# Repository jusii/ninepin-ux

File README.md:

# Ninepin UX

A USB and Bluetooth HID bridge for retro computers. USB and Bluetooth keyboards, mice and game
controllers on a Commodore Amiga or a C64, with the real Amiga keyboard passed through alongside
them. Over Wi-Fi, a PiKVM-compatible API lets scripts and LLM agents type and move the mouse.
Over USB-C the board is a USB adapter for a PC, a Mac or a C64 Ultimate.

Originally based on [borb/amigahid-pico](https://github.com/borb/amigahid-pico).

## boards

| board | what | state |
|---|---|---|
| **rev7.1** (`hardware/rev7.1/`) | rev7 + a reset supervisor on RUN (cold-plug fix) | current design, ordered |
| rev7 (tag `hw/ux-rev7`) | RP2350A + RM2 radio chip-down, 4 layers, 100 x 62 mm | built; needs the RUN bodge ([errata](./doc/errata.md)) |

rev7 and rev7.1 run the same firmware and fit the same case. Older boards: [history](./doc/history.md).

## features

* **Keyboard out** to the Amiga: mini-DIN6 (A4000D); DIN5 machines (A2000, A3000, A4000T) through
  a DIN5-to-mini-DIN6 cable; A500 header.
* **Real Amiga keyboard in** (mini-DIN6 or A500 header), merged with USB and Bluetooth input.
  Ctrl-Amiga-Amiga resets the Amiga for as long as it is held.
* **USB host** (USB-A, hubs): keyboards, mice, game controllers.
* **Bluetooth** (RM2 / CYW43439): Classic and LE keyboards, mice and controllers.
* **Game controllers:** PS5 DualSense (USB, Bluetooth), PS4 DualShock 4 (Bluetooth), PS3
  DualShock 3 (USB), generic HID pads. Two players, swap, merge, deadzone, autofire, DualSense
  touchpad as mouse.
* **Pad combos and profiles:** a pad button stands for directions and fire held together, a
  keyboard key, or both; 32 named profiles, each for the Amiga, the C64 or both, switched from
  the page, the menu or the pad.
* **Three modes:** `amiga` (keyboards to the Amiga, mouse and pads to the DE9 ports), `c64`
  (keyboard and mouse to USB-C, pads to the DE9 ports), `usb` (everything, the Amiga keyboard
  included, to USB-C for a PC or Mac).
* **DE9 ports, Amiga:** mouse (TankMouse / Cocolino wheel), joystick with 3 fire buttons, CD32 pad.
* **DE9 ports, C64:** joystick with 2nd / 3rd fire on the POT lines, 1351 mouse.
* **USB-C device:** keyboard, mouse, two gamepads, serial console.
* **Keyboard settings:** Help / Del / ISO key mapping, Y-Z and AZERTY presets, 8 remaps each way.
* **Menu** on the OLED, in two levels, from a keyboard, the BOOT button, a rotary encoder, a
  PlayStation pad or the console.
* **Wi-Fi:** access point or joins a network; settings page (no JavaScript) with every menu
  setting, a log-in with the page password, the board's uptime and why it last restarted.
* **Network control:** a subset of the PiKVM `kvmd` HTTP API (keys, text in six keymaps, mouse).
* **Firmware updates:** A/B slots with rollback; from the latest signed release on GitHub when
  asked, or a file uploaded on the settings page; with or without a press of BOOT on the board.

## docs

* [user guide](./doc/user-guide.md): connecting, first install, modes, menu, pads, Bluetooth,
  Wi-Fi, network control, updates.
* [board](./doc/board.md): connectors, power, encoder, OLED.
* [build](./doc/build.md): firmware build, ordering and assembling a board, the case.
* [errata](./doc/errata.md): read before building.
* [history](./doc/history.md): earlier boards and where their files are.

Firmware downloads: [Releases](https://github.com/jusii/ninepin-ux/releases).

## repository

| path | what |
|---|---|
| `firmware/` | firmware source, CMake build, pico-sdk and library submodules |
| `hardware/rev7.1/` | KiCad project and generator scripts, `fab/` (JLCPCB package), `bom/` (hand-fit parts, ibom) |
| `hardware/case/` | 3D-printable case (STL, STEP, FreeCAD) and its generator |
| `tools/` | board checkers, bench scripts |
| `doc/` | the guides above |

## credits

* **nine (borb)**: the original [amigahid](https://github.com/borb/amigahid) and
  [amigahid-pico](https://github.com/borb/amigahid-pico): the idea, the Amiga keyboard and
  quadrature code, the rev 2-5 boards.
* **Stefan Reinauer**: Bluetooth HID host, mouse-motion rewrite, input bridge, SDK/TinyUSB/CYW43
  update ([#44](https://github.com/borb/amigahid-pico/pull/44),
  [#47](https://github.com/borb/amigahid-pico/pull/47),
  [#48](https://github.com/borb/amigahid-pico/pull/48),
  [#49](https://github.com/borb/amigahid-pico/pull/49)). The settings store, gamepad parser, PS3,
  DualShock 4, CD32 and menu input handling are ported from his
  [reinauer/amigahid-pico](https://github.com/reinauer/amigahid-pico).
* **fboldog**: SH1106 1.3" OLED support ([#46](https://github.com/borb/amigahid-pico/pull/46)).
* **BennehBoy**, **rfuest**: keyboard fixes upstream.
* µgui by Achim Döbler, see the [display readme](./firmware/src/display/README.md).

An LLM assistant was used throughout this project, for the board layout, the checker scripts,
the firmware and these docs. Every result was reviewed, built and tested by hand.

## license

* Firmware and tools: Eclipse Public License 2.0 ([LICENSE](./LICENSE)), inherited from upstream.
* Hardware (`hardware/`: boards and case): CERN-OHL-W-2.0 ([hardware/LICENSE](./hardware/LICENSE)).

Jusii: boards, case, keyboard passthrough, rev7 firmware.

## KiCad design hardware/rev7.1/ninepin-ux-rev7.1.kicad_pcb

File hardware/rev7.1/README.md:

# Ninepin UX rev7.1

rev7 plus **U11, a TLV803S reset supervisor on RUN**. Same firmware, outline, connectors, case
(`../case/`) and hand-fitted parts as rev7 (tag `hw/ux-rev7`). Ordering and assembly:
[doc/build.md](../../doc/build.md).

## changes from rev7

* **U11 TLV803SDBZR (LCSC C132016) + C40 100 nF**, south of the OLED. U11 holds RUN low until 3V3
  has been above 2.93 V for 200 ms, and again whenever 3V3 sags below that: no more cold-plug
  BOOTSEL. Open drain, wired-OR with SW2 on `run_sw`. New copper is `route.py` block 5 only.
* R70/R71 use C25190, the same 27R as R57/R58.
* L1 is the Abracon AOTA-B201610S3R3-101-T the land was drawn for.
* `fab/make_fab.py`: JLC rotation offsets from the rev7 order preview; SMT-only recipe.

If U11 misbehaves: remove it and fit 1 µF + 1 MΩ across SW2 pins 1-2 on the back.

## regenerate and check

From the repository root. KiCad 10 with its Python `pcbnew`; FreeCAD for the case.

```shell
cd hardware/rev7.1 && python3 make_sch.py && python3 make_board.py --force && python3 route.py && cd ../..
P=hardware/rev7.1/ninepin-ux-rev7.1
kicad-cli sch erc $P.kicad_sch --exit-code-violations
kicad-cli pcb drc $P.kicad_pcb --schematic-parity --severity-all --refill-zones --save-board --exit-code-violations
git checkout -- $P.kicad_pro $P.kicad_prl     # kicad-cli rewrites them
python3 tools/check_rev7_1_pcb.py && python3 tools/check_rev7_1_netlist.py && python3 tools/check_rev7_1_style.py
python3 hardware/rev7.1/fab/make_fab.py       # SMT-only and full-assembly BOM/CPL; gerbers only re-cut if the board changed
python3 tools/check_rev7_1_fab.py             # the fab package matches the board
python3 hardware/case/run_case.py             # case STLs and fit report
```

`bom/ibom.html` comes from the InteractiveHtmlBom plugin
(`generate_interactive_bom.py --no-browser --dest-dir bom --name-format ibom --highlight-pin1 all
--checkboxes Sourced,Placed --bom-view top-bottom --layer-view F --show-fields Value,Footprint
--blacklist 'H*' ninepin-ux-rev7.1.kicad_pcb`).

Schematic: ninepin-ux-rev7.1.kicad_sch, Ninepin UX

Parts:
C1: 22uF; C_0805_2012Metric; LCSC C45783
C2, C6, C10, C14: 10uF; C_0805_2012Metric; LCSC C15850
C3, C5, C7, C11, C12, C13, C23, C24, C26, C27, C28, C32, C36: 100nF; C_0603_1608Metric; LCSC C14663
C4: 150uF; CP_Elec_6.3x7.7; MPN EEEFKC151XAP; LCSC C413656
C8, C9, C31: 1uF; C_0603_1608Metric; LCSC C15849
C20: 4.7uF; C_0402_1005Metric; LCSC C23733
C21, C22, C25, C30, C39, C40: 100nF; C_0402_1005Metric; LCSC C1525
C29, C38: 4.7uF; C_0402_1005Metric_vreg; LCSC C23733
C33, C34: 15pF; C_0603_1608Metric; LCSC C1644
C35: 4.7uF; C_0805_2012Metric; LCSC C1779
C37: 4.7uF; C_0603_1608Metric; LCSC C19666
D1, D2, D3: SS34; D_SMA; LCSC C8678
D4, D5, D6: B5819W; D_SOD-123; LCSC C8598
D10, D11, D12, D20, D21, D22, D23, D24, D25, D26, D27, D28, D29, D30: PESD5V0S1BA; D_SOD-323; LCSC C19224
D13, D14, D15, D16, D17, D18, D19: PESD5V0S1BL; D_SOD-882; MPN PESD5V0S1BL,315; LCSC C84374
F1: 750mA; Fuse_1812_4532Metric; MPN MF-MSMF075-2; LCSC C84140
F2, F3: 500mA; Fuse_1812_4532Metric; MPN MF-MSMF050-2; LCSC C17313
FB1: 600R@100MHz; L_0603_1608Metric; MPN BLM18AG601SN1D; LCSC C19330
J1: A500 KBD OUT; PinHeader_1x08_P2.54mm_Vertical; LCSC C492407
J2: SWD; PinHeader_1x03_P2.54mm_Vertical; LCSC C2937625
J3: OLED; PinSocket_1x04_P2.54mm_Vertical; MPN PM254-1-04-Z-8.5; LCSC C2897367
J4: USB-A HOST; USB_A_Molex_67643_Horizontal; MPN Molex 676432910; LCSC C564920
J7: ENCODER; PinHeader_2x03_P2.54mm_Vertical; MPN BOOMELE 2.54-2*3P; LCSC C65114
J8: A500 KBD IN; PinHeader_1x08_P2.54mm_Vertical; LCSC C492407
J10: KBD OUT (to Amiga); MiniDIN6_PS2_Socket_CUI_MD-60S; MPN CUI MD-60S; LCSC C6089346
J12: KBD IN (from keyboard); MiniDIN6_PS2_Socket_CUI_MD-60S; MPN CUI MD-60S; LCSC C6089346
J13: USB-C; USB_C_Receptacle_GCT_USB4105-xx-A_16P_TopMnt_Horizontal; MPN GCT USB4105-GF-A-120; LCSC C5184243
JP1: KBIN PWRLED; SolderJumper-2_P1.3mm_Open_RoundedPad1.0x1.5mm
L1: 3.3uH; L_2016_AOTA; MPN AOTA-B201610S3R3-101-T; LCSC C42411119
LED1: WS2812B-2020; LED_WS2812B-2020_PLCC4_2.0x2.0mm; LCSC C52917434
P1: DE9 PORT 1; DSUB-9_Pins_Horizontal_P2.77x2.84mm_EdgePinOffset7.70mm_Hou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; MPN TE 5747840-4; LCSC C305939
P2: DE9 PORT 2; DSUB-9_Pins_Horizontal_P2.77x2.84mm_EdgePinOffset7.70mm_Hou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; MPN TE 5747840-4; LCSC C305939
Q1: 2N7002; SOT-23; LCSC C8545
Q2, Q3: BSS138; SOT-23; LCSC C82045
R41, R42, R68: 4.7k; R_0603_1608Metric; LCSC C23162
R43, R44: 5.1k; R_0603_1608Metric; LCSC C23186
R45, R55: 470; R_0603_1608Metric; LCSC C23179
R46, R47: 100k; R_0603_1608Metric; LCSC C25803
R49, R52, R53, R54, R60: 1k; R_0603_1608Metric; LCSC C21190
R50, R59: 33; R_0603_1608Metric; LCSC C23140
R56, R69: 10k; R_0603_1608Metric; LCSC C25804
R57, R58, R70, R71: 27; R_0603_1608Metric; LCSC C25190
R61, R62, R63, R64, R65, R66, R67: 10k; R_0402_1005Metric; LCSC C25744
R72, R73: 15k; R_0402_1005Metric; LCSC C25756
RN1, RN2, RN4: 4x10k; R_Array_Convex_4x0402; LCSC C25725
RN3: 4x10k; R_Array_Convex_4x0603; LCSC C29718
SW1: BOOT; SW_Tactile_SPST_Angled_PTS645Vx58-2LFS; MPN C&K PTS645VK392LFS; LCSC C285519
SW2: RESET; SW_Tactile_SPST_Angled_PTS645Vx58-2LFS; MPN C&K PTS645VK392LFS; LCSC C285519
U1: RP2350A; QFN-60-1EP_7x7mm_P0.4mm_EP3.4x3.4mm; LCSC C42411118
U2, U4: USBLC6-2SC6; SOT-23-6; LCSC C7519
U3: TLV75733PDRVR; WSON-6-1EP_2x2mm_P0.65mm_EP1x1.6mm; LCSC C2868428
U6, U7: SN74CBTD3861DBQR; SSOP-24_3.9x8.7mm_P0.635mm; LCSC C44508
U8: W25Q128JVSIQ; SOIC-8_5.3x5.3mm_P1.27mm; LCSC C97521
U9: RM2; RaspberryPi_RM2; MPN Raspberry Pi RM2; LCSC C49451547
U10: TCA9554PWR; TSSOP-16_4.4x5mm_P0.65mm; LCSC C477924
U11: TLV803SDBZR; SOT-23; MPN TLV803SDBZR; LCSC C132016
Y1: 12MHz; Crystal_SMD_3225-4Pin_3.2x2.5mm; MPN ABM8-272-T3; LCSC C20625731

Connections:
/+3V3: C9.1, C10.1, C23.1, C24.1, C25.1, C26.1, C27.1, C28.1, C29.1, C30.1, C32.1, C39.1, C40.1, FB1.1, J3.2, J7.6, Q2.1 (G), Q3.1 (G), R41.1, R42.1, R50.1, R59.1, U1.1 (IOVDD), U1.11 (IOVDD), U1.20 (IOVDD), U1.30 (IOVDD), U1.38 (IOVDD), U1.45 (IOVDD), U1.49 (VREG_VIN), U1.53 (USB_OTP_VDD), U1.54 (QSPI_IOVDD), U3.1 (OUT), U8.8 (VCC), U10.16 (VDD), U11.3 (VCC)
/AMIGA_5V: D4.2 (A), F1.1, J1.4, J10.4
/AMIGA_5V_FUSED: D1.2 (A), F1.2, R60.1
/AMIGA_IO5V: C13.1, C14.1, D4.1 (K), D5.1 (K), D6.1 (K), R46.1, R61.2, R62.2, R63.2, R64.2, R65.2, R66.2, R67.2, RN1.5 (R4.2), RN1.6 (R3.2), RN1.7 (R2.2), RN1.8 (R1.2), RN2.5 (R4.2), RN2.6 (R3.2), RN2.7 (R2.2), RN2.8 (R1.2), RN3.5 (R4.2), RN3.6 (R3.2), RN3.7 (R2.2), RN3.8 (R1.2), U6.24 (VCC), U7.24 (VCC)
/AUX_5V: D2.2 (A), J13.A4 (VBUS), J13.A9 (VBUS), J13.B4 (VBUS), J13.B9 (VBUS), R68.1, U4.5 (VBUS)
/KBIN_5V: C6.1, C7.1, F3.2, J8.4, J12.4, RN4.5 (R4.2), RN4.6 (R3.2), RN4.7 (R2.2), RN4.8 (R1.2)
/LED_VDD: C12.1, D3.1 (K), LED1.4 (VDD), R49.1
/SYS5V: C1.1, C2.1, C3.1, C8.1, D1.1 (K), D2.1 (K), D3.2 (A), F2.1, F3.1, R45.2, U3.4 (EN), U3.6 (IN)
/USBA_5V: C4.1, C5.1, F2.2, J4.1 (VBUS), U2.5 (VBUS)
/adc_avdd: C31.1, R50.2, U1.44 (ADC_AVDD)
/amiga_sense: C11.1, R46.2, R47.1, U1.42 (GPIO28/ADC2)
/cont1_5v: D5.2 (A), P1.7
/cont1_b1: D16.1 (A1), P1.6, RN1.1 (R1.1), U6.8 (A7)
/cont1_b1_lo: U1.14 (GPIO10), U6.16 (B7)
/cont1_b2: D14.1 (A1), P1.9, RN1.3 (R3.1), U6.6 (A5)
/cont1_b2_lo: U1.12 (GPIO8), U6.18 (B5)
/cont1_b3: D13.1 (A1), P1.5, RN1.4 (R4.1), U6.5 (A4)
/cont1_b3_lo: U1.10 (GPIO7), U6.19 (B4)
/cont1_h: D17.1 (A1), P1.2, RN2.4 (R4.1), U6.9 (A8)
/cont1_h_lo: U1.15 (GPIO11), U6.15 (B8)
/cont1_hq: D19.1 (A1), P1.4, RN2.2 (R2.1), U6.11 (A10)
/cont1_hq_lo: U1.17 (GPIO13), U6.13 (B10)
/cont1_v: D15.1 (A1), P1.1, RN1.2 (R2.1), U6.7 (A6)
/cont1_v_lo: U1.13 (GPIO9), U6.17 (B6)
/cont1_vq: D18.1 (A1), P1.3, RN2.3 (R3.1), U6.10 (A9)
/cont1_vq_lo: U1.16 (GPIO12), U6.14 (B9)
/cont2_5v: D6.2 (A), P2.7
/cont2_b1: D23.1 (A1), P2.6, R62.1, U7.5 (A4)
/cont2_b1_lo: U1.28 (GPIO17), U7.19 (B4)
/cont2_b2: D27.1 (A1), P2.9, R66.1, U7.9 (A8)
/cont2_b2_lo: U1.33 (GPIO21), U7.15 (B8)
/cont2_b3: D28.1 (A1), P2.5, R67.1, U7.10 (A9)
/cont2_b3_lo: U1.34 (GPIO22), U7.14 (B9)
/cont2_h: D24.1 (A1), P2.2, R63.1, U7.6 (A5)
/cont2_h_lo: U1.29 (GPIO18), U7.18 (B5)
/cont2_hq: D26.1 (A1), P2.4, R65.1, U7.8 (A7)
/cont2_hq_lo: U1.32 (GPIO20), U7.16 (B7)
/cont2_v: D22.1 (A1), P2.1, R61.1, U7.4 (A3)
/cont2_v_lo: U1.27 (GPIO16), U7.20 (B3)
/cont2_vq: D25.1 (A1), P2.3, R64.1, U7.7 (A6)
/cont2_vq_lo: U1.31 (GPIO19), U7.17 (B6)
/dvdd: C20.1, C21.1, C22.1, C38.1, L1.1, U1.6 (DVDD), U1.23 (DVDD), U1.39 (DVDD), U1.50 (VREG_FB)
/enc_a: J7.5, U10.4 (P0)
/enc_b: J7.3, U10.5 (P1)
/enc_sp: J7.2, U10.7 (P3)
/enc_sw: J7.1, U10.6 (P2)
/exp_int: U1.5 (GPIO3), U10.13 (~INT)
/i2c_scl: J3.3, R42.2, U1.3 (GPIO1), U10.14 (SCL)
/i2c_sda: J3.4, R41.2, U1.2 (GPIO0), U10.15 (SDA)
/kb_drvled: D30.1 (A1), J1.8, J8.8
/kb_pwrled: D29.1 (A1), J1.7, J8.7, JP1.1 (A)
/kb_pwrled_bal: JP1.2 (B), R45.1
/kbclock: D12.1 (A1), J1.1, J10.5, RN3.3 (R3.1), U6.4 (A3)
/kbclock_lo: U1.9 (GPIO6), U6.20 (B3)
/kbdata: D11.1 (A1), J1.2, J10.1, RN3.2 (R2.1), U6.3 (A2)
/kbdata_lo: U1.8 (GPIO5), U6.21 (B2)
/kbin_clk: D20.1 (A1), J8.1, J12.5, Q3.3 (D), RN4.4 (R4.1)
/kbin_clk_lo: Q3.2 (S), U1.18 (GPIO14)
/kbin_dat: D21.1 (A1), J8.2, J12.1, Q2.3 (D), RN4.3 (R3.1)
/kbin_dat_lo: Q2.2 (S), U1.19 (GPIO15)
/kbreset: D10.1 (A1), J1.3, J8.3, U6.2 (A1)
/kbreset_lo: U1.7 (GPIO4), U6.22 (B1)
/pio_dm: R71.1, R73.1, U1.41 (GPIO27/ADC1)
/pio_dp: R70.1, R72.1, U1.40 (GPIO26/ADC0)
/qspi_sclk: U1.56 (QSPI_SCLK), U8.6 (CLK)
/qspi_sd0: U1.57 (QSPI_SD0), U8.5 (DI/IO_{0})
/qspi_sd1: U1.59 (QSPI_SD1), U8.2 (DO/IO_{1})
/qspi_sd2: U1.58 (QSPI_SD2), U8.3 (~WP/IO_{2})
/qspi_sd3: U1.55 (QSPI_SD3), U8.7 (~HOLD/~RESET/IO_{3})
/qspi_ss: R52.1, U1.60 (~QSPI_SS), U8.1 (~CS)
/qspi_ss_sw: R52.2, SW1.1
/run: R53.1, U1.26 (RUN)
/run_sw: R53.2, SW2.1, U11.2 (~RESET)
/swclk: J2.1, U1.24 (SWCLK)
/swdio: J2.3, U1.25 (SWDIO)
/usb_cc1: J13.A5 (CC1), R43.1
/usb_cc2: J13.B5 (CC2), R44.1
/usb_dm: R58.1, U1.51 (USB_DM)
/usb_dp: R57.1, U1.52 (USB_DP)
/usba_dm: J4.2 (D-), R71.2, U2.1 (I/O1), U2.6 (I/O1)
/usba_dp: J4.3 (D+), R70.2, U2.3 (I/O2), U2.4 (I/O2)
/usbc_dm: J13.A7 (D-), J13.B7 (D-), R58.2, U4.1 (I/O1), U4.6 (I/O1)
/usbc_dp: J13.A6 (D+), J13.B6 (D+), R57.2, U4.3 (I/O2), U4.4 (I/O2)
/vbus_sense: R68.2, R69.1, U10.9 (P4)
/vreg_avdd: C37.1, R59.2, U1.46 (VREG_AVDD)
/vreg_lx: L1.2, U1.48 (VREG_LX)
/wl_clk: U1.43 (GPIO29/ADC3), U9.3 (SCLK)
/wl_cs: U1.37 (GPIO25), U9.9 (CS)
/wl_d: R55.2, R56.2, U1.36 (GPIO24), U9.5 (DIN)
/wl_dout: R55.1, U9.6 (DOUT)
/wl_irq: R56.1, U9.10 (nIRQ)
/wl_on: U1.35 (GPIO23), U9.12 (WL_ON), U9.13 (BT_ON)
/wl_vin: C35.1, C36.1, FB1.2, U9.14 (VDDIO), U9.16 (VIN)
/ws_din: LED1.3 (DIN), Q1.3 (D), R49.2
/ws_drv: Q1.1 (G), U1.4 (GPIO2)
/xin: C33.1, U1.21 (XIN), Y1.1
/xout: R54.1, U1.22 (XOUT)
/xout_r: C34.1, R54.2, Y1.3
GND: C1.2, C2.2, C3.2, C4.2, C5.2, C6.2, C7.2, C8.2, C9.2, C10.2, C11.2, C12.2, C13.2, C14.2, C20.2, C21.2, C22.2, C23.2, C24.2, C25.2, C26.2, C27.2, C28.2, C29.2, C30.2, C31.2, C32.2, C33.2, C34.2, C35.2, C36.2, C37.2, C38.2, C39.2, C40.2, D10.2 (A2), D11.2 (A2), D12.2 (A2), D13.2 (A2), D14.2 (A2), D15.2 (A2), D16.2 (A2), D17.2 (A2), D18.2 (A2), D19.2 (A2), D20.2 (A2), D21.2 (A2), D22.2 (A2), D23.2 (A2), D24.2 (A2), D25.2 (A2), D26.2 (A2), D27.2 (A2), D28.2 (A2), D29.2 (A2), D30.2 (A2), J1.6, J2.2, J3.1, J4.4 (GND), J4.SH (Shield), J7.4, J8.6, J10.3, J10.SH (SHIELD), J12.3, J12.SH (SHIELD), J13.A1 (GND), J13.A12 (GND), J13.B1 (GND), J13.B12 (GND), J13.SH (SHIELD), LED1.2 (VSS), P1.8, P1.SH (PAD), P2.8, P2.SH (PAD), Q1.2 (S), R43.2, R44.2, R47.2, R60.2, R69.2, R72.2, R73.2, SW1.2, SW2.2, U1.47 (VREG_PGND), U1.61 (GND), U2.2 (GND), U3.3 (GND), U3.7 (GND), U4.2 (GND), U6.12 (GND), U6.23 (~OE), U7.12 (GND), U7.23 (~OE), U8.4 (GND), U9.1 (GND), U9.4 (GND), U9.7 (GND), U9.11 (GND), U9.15 (GND), U9.21 (GND), U10.1 (A0), U10.2 (A1), U10.3 (A2), U10.8 (GND), U11.1 (GND), Y1.2 (G), Y1.4 (G)

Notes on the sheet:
power tree
AMIGA_5V (keyboard connector / A500 header) -> F1 -> AMIGA_5V_FUSED -> D1 -> SYS5V; USB-C -> D2 -> SYS5V. Either source alone runs the board.
AMIGA_IO5V (2026-10-16) is the bus-switch / pull-up / Amiga-sense rail: OR-ed through D4 from AMIGA_5V (before F1, so the switches stay above their 4.5 V minimum; the rail draws ~20 mA and the DE9 legs are unfused anyway) and through D5 / D6 from DE9 pin 7 of each port, so the ports work with only 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
F1 750 mA fitted (rev6 bring-up measured the stack well under that). SYS5V -> U3 -> +3V3 (RP2350, RM2, flash, OLED, expander). R60 bleeds D1 leakage off the fused rail.
to amiga (keyboard out) / from real keyboard (keyboard in) / A500 headers
Mini-DIN6 uses the PS/2 pin positions: 1 KDAT, 3 GND, 4 +5 V, 5 KCLK. DIN5 Amigas use a passive adapter.
JP1 is for standalone use only (no Amiga on J1): bridges the A500 keyboard power LED through R45.
controller ports (DE9 male, straight-through F-F cables)
Pin 7 (+5 V) feeds only the I/O rail through D5 / D6: the ports power the bus switches and pull-ups, never the board itself.
level shifting: 2x SN74CBTD3861 bus switches, Amiga side on A, RP2350 side on B
VCC = AMIGA_IO5V (keyboard-connector 5 V or either DE9 pin 7, through D4-D6): the diode-dropped gate limits the B side to ~2.6-3.0 V typ (TI fig. 2) and the RP2350 internal pull-up completes the rise to 3.3 V. OE tied low (always on). VCC is one Schottky drop below the Amiga's 5 V (~4.5-4.8 V); D4 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
Keyboard-in (kbin_clk / kbin_dat) is not on U7 any more: Q2 / Q3 BSS138 shifters with RN4 on KBIN_5V and the RP2350 internal pull-ups on the GPIO side, so a real Amiga keyboard reads on USB-C power alone (device mode for a C64 Ultimate); U7 A1/A2 and B1/B2 are left open.
With the Amiga off the switches are open and the B side floats: firmware enables the RP2350 internal pull-ups on every _lo input.
Amiga-side pull-ups: 10k to AMIGA_IO5V - four 4-element arrays (RN1-RN3, RN4 on KBIN_5V) and seven 0402 resistors on the port-2 lines; kbreset has none. ESD clamps D10-D28 on every Amiga-facing line; the I/O rail itself takes an ESD hit on DE9 pin 7 into C14 (10 uF).
usb: USB-C on the RP2350 USB PHY (device, power, flashing), USB-A host on PIO-USB (GPIO26/27)
No mux (decided 2026-10-15): the native PHY serves USB-C, so the board can be a HID device for a USB host (Commodore 64 Ultimate) while USB-A stays a host on PIO-USB. USB-C is device-only: CC carries Rd and VBUS only flows in through D2 (review 2026-10-15).
USB-C is a UFP: 5.1k on each CC. VBUS -> AUX_5V -> D2 -> SYS5V. USB-A VBUS is SYS5V through F2.
mcu: RP2350A, 16 MB QSPI flash, 12 MHz crystal, BOOT / RESET, SWD
Per the RP2350 hardware design guide / Pico 2 W: VREG_VIN and VREG_AVDD on 3V3 (AVDD through 33R + 4.7uF), DVDD 4.7uF at pin 23 + 100nF at 6/39, 4.7uF CIN at VREG_VIN, 100nF per IOVDD pin, one 100nF shared by USB_OTP_VDD/QSPI_IOVDD.
BOOT pulls QSPI_SS low at reset (USB bootloader on USB-C); RESET pulls RUN low.
rev7.1: U11 (TLV803S, 2.93 V / 200 ms, open drain) also holds run_sw low until 3V3 is up and on brown-out.
radio: RM2 (CYW43439) on the Pico 2 W pin assignment
wl_d is the shared data line: DIN direct, DOUT through 470R, nIRQ through 10k, as on the Pico 2 W. WL_ON and BT_ON tied to GPIO23.
VIN and VDDIO from +3V3 through FB1. The module's own GPIO0-2 are unused.
display / status / spare
OLED posts H5-H8: copper passes 0.2 mm from the M2 holes under the post bases, so the posts, screws and nuts must be nylon (never metal hardware here).
J3 pin order is the common 0.96in SSD1306 module: GND VCC SCL SDA. LED1 is the only indicator: GPIO2 (output inverted in firmware) -> Q1 -> ws_din swings the full LED_VDD so the WS2812 VIH is met.

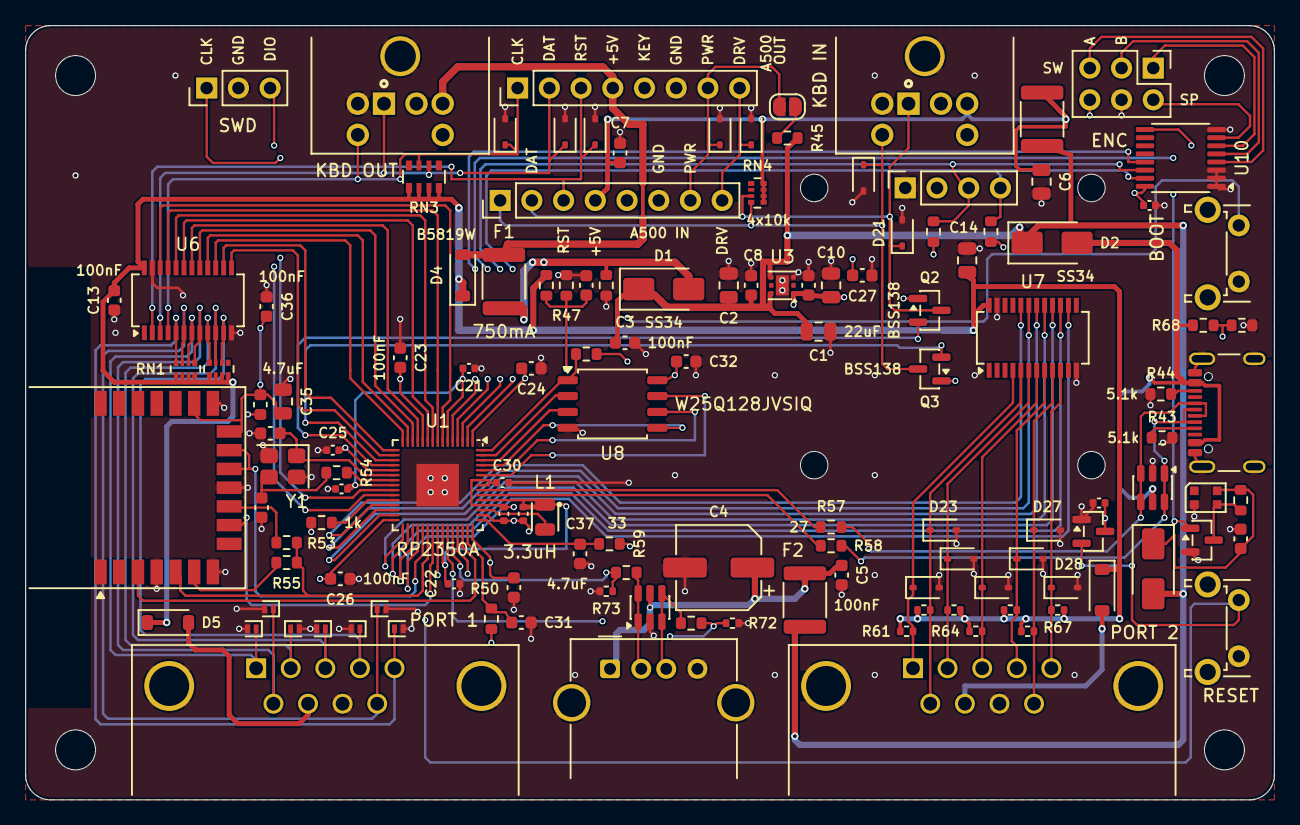
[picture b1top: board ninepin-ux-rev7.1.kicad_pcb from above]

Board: 4 copper layers, 100.0 x 62.0 mm, 139 parts (0 on the bottom side), 99 nets.

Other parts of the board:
H1, H2, H3, H4: M3; MountingHole_3.2mm_M3
H5, H6, H7, H8: M2 OLED post; MountingHole_2.2mm_M2

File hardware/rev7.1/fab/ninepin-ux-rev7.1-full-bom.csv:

Comment,Designator,Footprint,LCSC Part #
22uF,C1,C_0805_2012Metric,C45783
10uF,"C2,C6,C10,C14",C_0805_2012Metric,C15850
100nF,"C3,C5,C7,C11,C12,C13,C23,C24,C26,C27,C28,C32,C36",C_0603_1608Metric,C14663
150uF,C4,CP_Elec_6.3x7.7,C413656
1uF,"C8,C9,C31",C_0603_1608Metric,C15849
4.7uF,"C20,C29,C38",C_0402_1005Metric,C23733
100nF,"C21,C22,C25,C30,C39,C40",C_0402_1005Metric,C1525
15pF,"C33,C34",C_0603_1608Metric,C1644
4.7uF,C35,C_0805_2012Metric,C1779
4.7uF,C37,C_0603_1608Metric,C19666
SS34,"D1,D2,D3",D_SMA,C8678
B5819W,"D4,D5,D6",D_SOD-123,C8598
PESD5V0S1BA,"D10,D11,D12,D20,D21,D22,D23,D24,D25,D26,D27,D28,D29,D30",D_SOD-323,C19224
PESD5V0S1BL,"D13,D14,D15,D16,D17,D18,D19",D_SOD-882,C84374
750mA,F1,Fuse_1812_4532Metric,C84140
500mA,"F2,F3",Fuse_1812_4532Metric,C17313
600R@100MHz,FB1,L_0603_1608Metric,C19330
A500 KBD OUT,"J1,J8",PinHeader_1x08_P2.54mm_Vertical,C492407
SWD,J2,PinHeader_1x03_P2.54mm_Vertical,C2937625
OLED,J3,PinSocket_1x04_P2.54mm_Vertical,C2897367
USB-A HOST,J4,USB_A_Molex_67643_Horizontal,C564920
ENCODER,J7,PinHeader_2x03_P2.54mm_Vertical,C65114
KBD OUT (to Amiga),"J10,J12",MiniDIN6_PS2_Socket_CUI_MD-60S,C6089346
USB-C,J13,USB_C_Receptacle_GCT_USB4105-xx-A_16P_TopMnt_Horizontal,C5184243
3.3uH,L1,L_2016_AOTA,C42411119
WS2812B-2020,LED1,LED_WS2812B-2020_PLCC4_2.0x2.0mm,C52917434
DE9 PORT 1,"P1,P2",DSUB-9_Pins_Horizontal_P2.77x2.84mm_EdgePinOffset7.70mm_Housed_MountingHolesOffset9.12mm,C305939
2N7002,Q1,SOT-23,C8545
BSS138,"Q2,Q3",SOT-23,C82045
4.7k,"R41,R42,R68",R_0603_1608Metric,C23162
5.1k,"R43,R44",R_0603_1608Metric,C23186
470,"R45,R55",R_0603_1608Metric,C23179
100k,"R46,R47",R_0603_1608Metric,C25803
1k,"R49,R52,R53,R54,R60",R_0603_1608Metric,C21190
33,"R50,R59",R_0603_1608Metric,C23140
10k,"R56,R69",R_0603_1608Metric,C25804
27,"R57,R58,R70,R71",R_0603_1608Metric,C25190
10k,"R61,R62,R63,R64,R65,R66,R67",R_0402_1005Metric,C25744
15k,"R72,R73",R_0402_1005Metric,C25756
4x10k,"RN1,RN2,RN4",R_Array_Convex_4x0402,C25725
4x10k,RN3,R_Array_Convex_4x0603,C29718
BOOT,"SW1,SW2",SW_Tactile_SPST_Angled_PTS645Vx58-2LFS,C285519
RP2350A,U1,QFN-60-1EP_7x7mm_P0.4mm_EP3.4x3.4mm,C42411118
USBLC6-2SC6,"U2,U4",SOT-23-6,C7519
TLV75733PDRVR,U3,WSON-6-1EP_2x2mm_P0.65mm_EP1x1.6mm,C2868428
SN74CBTD3861DBQR,"U6,U7",SSOP-24_3.9x8.7mm_P0.635mm,C44508
W25Q128JVSIQ,U8,SOIC-8_5.3x5.3mm_P1.27mm,C97521
RM2,U9,RaspberryPi_RM2,C49451547
TCA9554PWR,U10,TSSOP-16_4.4x5mm_P0.65mm,C477924
TLV803SDBZR,U11,SOT-23,C132016
12MHz,Y1,Crystal_SMD_3225-4Pin_3.2x2.5mm,C20625731

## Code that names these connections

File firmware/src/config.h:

/**
 * this file is part of amigahid-pico, (c) 2021 just nine <nine@aphlor.org>
 * please locate the full source at https://github.com/borb/amigahid-pico
 *
 * released under the terms of the Eclipse Public License 2.0 (EPL-2.0).
 * please find the complete license text at https://spdx.org/licenses/EPL-2.0
 *
 * board configuration
 *
 * PLEASE NOTE ALL PIN DESIGNATIONS ARE GPIO PIN NUMBERS - NOT PHYSICAL PIN NUMBERS
 */

#ifndef _CONFIG_H
#define _CONFIG_H

#if defined(BOARD_HIDPICO_REV7)
// ninepin ux rev7 and rev7.1 (same pin map; rev7.1 only adds a reset supervisor).
// chip-down rp2350a + rm2 (sdk board header: boards/amigahid_rev7.h). this block
// is the single source of truth for the application pins; it mirrors the GPIO
// dict in hardware/rev7.1/design.py, so a gpio moved on the schematic is a one-line
// change here. the rm2 wireless pins (GPIO23 wl_on, 24 wl_d, 25 wl_cs, 29
// wl_clk) belong to the sdk and are set in the board header, not here.
#  define I2C_PORT      i2c0
#  define I2C_PIN_SDA   0       // i2c_sda (4.7k to 3v3 on the board)
#  define I2C_PIN_SCL   1       // i2c_scl
// the tca9554 sharing this bus is a 400 kHz (fast mode) part, so the bus runs at
// that rather than the 1 MHz the display alone would take; a fast-mode device is
// not specified to ignore fast-mode-plus traffic addressed to someone else
#  define I2C_BAUD      400000

#  define KBD_AMIGA_RST 4       // kbreset_lo
#  define KBD_AMIGA_DAT 5       // kbdata_lo
#  define KBD_AMIGA_CLK 6       // kbclock_lo

#  define QM1_AMIGA_B3  7       // cont1_b3_lo (GPIO7-13 follow the bus-switch pin order, see design.py)
#  define QM1_AMIGA_B2  8       // cont1_b2_lo
#  define QM1_AMIGA_V   9       // cont1_v_lo
#  define QM1_AMIGA_B1  10      // cont1_b1_lo
#  define QM1_AMIGA_H   11      // cont1_h_lo
#  define QM1_AMIGA_VQ  12      // cont1_vq_lo
#  define QM1_AMIGA_HQ  13      // cont1_hq_lo

// dedicated real amiga keyboard input (J12)
#  define KBD_REAL_CLK  14      // kbin_clk_lo, real keyboard kclk (input)
#  define KBD_REAL_DAT  15      // kbin_dat_lo, real keyboard kdat (bidirectional)

// controller port 2. note the order differs from port 1. both ports are
// driven by de9.c: mouse, joystick, cd32 pad (amiga), joystick or 1351 (c64)
#  define QM2_AMIGA_V   16      // cont2_v_lo (GPIO16-22: the ADC pins are not 5 V tolerant)
#  define QM2_AMIGA_B1  17      // cont2_b1_lo
#  define QM2_AMIGA_H   18      // cont2_h_lo
#  define QM2_AMIGA_VQ  19      // cont2_vq_lo
#  define QM2_AMIGA_HQ  20      // cont2_hq_lo
#  define QM2_AMIGA_B2  21      // cont2_b2_lo
#  define QM2_AMIGA_B3  22      // cont2_b3_lo

// one ws2812b-2020 status led; status_led.c paints the led 1 / led 2 states
// onto its green and blue channels
#  define LED_STATUS_WS2812 2   // ws_drv: gate of Q1 (2n7002 inverter, 1k pull-up to LED_VDD) -> led din
#  define LED_STATUS_WS2812_INVERT  // the inverter means the gpio output must be inverted

// the rp2350's native phy is on the usb-c
// connector (device port: flashing, debug cdc, and the hid-device mode for a
// host such as the commodore 64 ultimate), and the usb-a host port is driven by
// pio-usb on GPIO26 (D+) / GPIO27 (D-) through 27R and a usblc6. the pio-usb
// host must not take pio0, which keyboard_recv owns.
#  define PIO_USB_DP_PIN    26  // pio_dp (D- is always DP+1 for pio-usb)
#  define PIO_USB_PIO       2   // pio2, all of it: pio0 = keyboard_recv; the ws2812 skips this pio (status_led.c), cyw43 finds it full
// pio-usb bit-bangs full speed and needs clk_sys at a multiple of 12 MHz; the
// rp2350's 150 MHz default is not one. main() sets this before anything derives
// a divider from clk_sys (every pio, i2c and adc divider in this tree is computed
// at init from clock_get_hz(), none is hard-coded)
#  define PIO_USB_SYS_CLOCK_KHZ 120000

// the native usb phy is a device port on the usb-c connector: a composite cdc
// (debug console - there is no uart) + hid (keyboard, mouse, gamepad) device.
// its D+ pull-up is only presented while the expander sees usb-c vbus.
// wi-fi and the settings page share the rm2 with bluetooth: builds with the
// radio only (wifi.c)
#  ifdef ENABLE_BLUETOOTH_HID
#    define HAS_WIFI
#  endif
// a/b partition slots and try-before-you-buy images (ota.c): every build
// accepts itself after a clean start; uploads come over wi-fi where there is one
#  define USB_DEVICE_VID    0xcafe  // tinyusb's example vid; see the report's open questions
#  define USB_DEVICE_PID    0x4a50  // "JP"; arbitrary within the example space

// the BOOT button (SW1, qspi_ss through 1k) read back at runtime with the
// bootsel trick; see util/user_button.h for the constraints that come with it

// tca9554 i2c i/o expander at 0x20 on the oled bus: P0 enc_a, P1 enc_b, P2 enc_sw,
// P3 enc_spare (2x3 encoder header J7), P4 = usb-c vbus sense (4.7k/10k divider),
// P5-P7 unused (the tca9554's internal pull-ups hold them). /INT is open drain
// on GPIO3: enable the internal pull-up.
#  define IO_EXPANDER_ADDR  0x20
#  define IO_EXPANDER_INT   3   // exp_int
#  define IO_EXPANDER_P_ENC_A   0
#  define IO_EXPANDER_P_ENC_B   1
#  define IO_EXPANDER_P_ENC_SW  2
#  define IO_EXPANDER_P_ENC_SP  3
#  define IO_EXPANDER_P_VBUS    4

// amiga-on sense: 100k/100k divider (+100n) from AMIGA_IO5V, the rail the bus
// switches run on (one schottky below the amiga's 5 v, fed from the keyboard
// connector or either DE9 pin 7): about 2.2-2.4 v with the amiga on, 0 v off.
// ADC2 on GPIO28, which is not 5 v tolerant and sees the rail through 100k only.
// board_pins_init() parks the pad as an analogue input (no pulls, digital input
// off - also the RP2350-E9 precaution); thresholds ~1.5 v on / ~1.2 v off.
#  define AMIGA_SENSE_PIN   28  // amiga_sense
#  define AMIGA_SENSE_ADC   2
#  define AMIGA_SENSE_VREF_MV   3300    // adc_avdd is +3V3 through 33R
#  define AMIGA_SENSE_ON_MV     1500    // rising above this: the amiga is on
#  define AMIGA_SENSE_OFF_MV    1200    // falling below this: the amiga is off

// no 3v3-side pull-ups on the board: with the amiga off the cbtd3861 bus
// switches open and the rp2350 side floats, so every _lo line needs the internal
// pull-up; the keyboard-in lines sit behind bss138 shifters (Q2/Q3) whose source
// side is likewise pulled up here. board_pins_init() enables these before any
// driver touches the pins.
#  define BOARD_PULLUP_PINS { \
       KBD_AMIGA_RST, KBD_AMIGA_DAT, KBD_AMIGA_CLK, \
       QM1_AMIGA_HQ, QM1_AMIGA_VQ, QM1_AMIGA_H, QM1_AMIGA_V, \
       QM1_AMIGA_B1, QM1_AMIGA_B2, QM1_AMIGA_B3, \
       KBD_REAL_CLK, KBD_REAL_DAT, \
       QM2_AMIGA_HQ, QM2_AMIGA_VQ, QM2_AMIGA_H, QM2_AMIGA_V, \
       QM2_AMIGA_B1, QM2_AMIGA_B2, QM2_AMIGA_B3 }
#else
#  error Board type has not been defined; check cmake command line
#endif

#endif // _CONFIG_H

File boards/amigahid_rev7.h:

/**
 * this file is part of amigahid-pico, (c) 2021 just nine <nine@aphlor.org>
 * please locate the full source at https://github.com/borb/amigahid-pico
 *
 * released under the terms of the Eclipse Public License 2.0 (EPL-2.0).
 * please find the complete license text at https://spdx.org/licenses/EPL-2.0
 *
 * pico-sdk board header for the rev7 board: a chip-down rp2350a with a 16 MB
 * w25q128 qspi flash, a 12 MHz crystal and a raspberry pi rm2 (cyw43439) wired
 * exactly as on the pico 2 w. selected with -DPICO_BOARD=amigahid_rev7, which
 * the top-level CMakeLists.txt does for you when BOARD_TYPE=BOARD_HIDPICO_REV7.
 *
 * this only describes the chip, flash, clock and radio - everything the sdk
 * itself needs. the application pin map (keyboard, controller ports, status
 * led, usb mux, amiga sense) lives in src/config.h under BOARD_HIDPICO_REV7.
 */

// -----------------------------------------------------
// NOTE: THIS HEADER IS ALSO INCLUDED BY ASSEMBLER SO
//       SHOULD ONLY CONSIST OF PREPROCESSOR DIRECTIVES
// -----------------------------------------------------

#ifndef _BOARDS_AMIGAHID_REV7_H
#define _BOARDS_AMIGAHID_REV7_H

pico_board_cmake_set(PICO_PLATFORM, rp2350)
pico_board_cmake_set(PICO_CYW43_SUPPORTED, 1)

// For board detection
#define AMIGAHID_REV7

// --- RP2350 VARIANT ---
#define PICO_RP2350A 1

// --- CLOCK ---
// 12 MHz crystal (abm8-272-t3), the sdk default; spelt out for the reader
#ifndef XOSC_HZ
#define XOSC_HZ 12000000u
#endif

// --- UART --- (uart0 on its aux pins; UART_FUNCSEL_NUM picks GPIO_FUNC_UART_AUX)
#ifndef PICO_DEFAULT_UART
#define PICO_DEFAULT_UART 0
#endif
#ifndef PICO_DEFAULT_UART_TX_PIN
#define PICO_DEFAULT_UART_TX_PIN 2
#endif
#ifndef PICO_DEFAULT_UART_RX_PIN
#define PICO_DEFAULT_UART_RX_PIN 3
#endif

// --- LED ---
// no PICO_DEFAULT_LED_PIN: the only indicator is the ws2812 on GPIO16, which
// src/util/status_led.c drives itself. it is deliberately not advertised as
// PICO_DEFAULT_WS2812_PIN so that nothing in the sdk or tinyusb's bsp claims it.
// no CYW43_WL_GPIO_LED_PIN: the rm2 has no led on its wl gpios.

// --- I2C ---
// the oled is on i2c1, GPIO2/3 (see src/config.h); the sdk default instance is
// only used by sdk examples and is left at the pico 2 w values
#ifndef PICO_DEFAULT_I2C
#define PICO_DEFAULT_I2C 1
#endif
#ifndef PICO_DEFAULT_I2C_SDA_PIN
#define PICO_DEFAULT_I2C_SDA_PIN 2
#endif
#ifndef PICO_DEFAULT_I2C_SCL_PIN
#define PICO_DEFAULT_I2C_SCL_PIN 3
#endif

// --- SPI ---
// no default spi instance; every free gpio is spoken for

// --- FLASH ---
// w25q128jvsiq, 16 MB
#define PICO_BOOT_STAGE2_CHOOSE_W25Q080 1

#ifndef PICO_FLASH_SPI_CLKDIV
#define PICO_FLASH_SPI_CLKDIV 2
#endif

pico_board_cmake_set_default(PICO_FLASH_SIZE_BYTES, (16 * 1024 * 1024))
#ifndef PICO_FLASH_SIZE_BYTES
#define PICO_FLASH_SIZE_BYTES (16 * 1024 * 1024)
#endif

// the core regulator is the rp2350's own switcher; there is no external smps
// and so no PICO_SMPS_MODE_PIN

// --- CYW43 (RM2) ---
// same pin assignment as the pico 2 w. GPIO29 is wl_clk only: unlike the pico
// 2 w there is no vsys divider sharing it, so CYW43_USES_VSYS_PIN and
// PICO_VSYS_PIN are not defined. the rm2's wl gpio0-2 are unconnected, so there
// is no CYW43_WL_GPIO_LED_PIN, CYW43_WL_GPIO_SMPS_PIN or CYW43_WL_GPIO_VBUS_PIN.
#ifndef CYW43_WL_GPIO_COUNT
#define CYW43_WL_GPIO_COUNT 3
#endif

// cyw43 SPI pins can't be changed at runtime
#ifndef CYW43_PIN_WL_DYNAMIC
#define CYW43_PIN_WL_DYNAMIC 0
#endif

// gpio pin to power up the cyw43 chip (WL_ON and BT_ON both tied to it)
#ifndef CYW43_DEFAULT_PIN_WL_REG_ON
#define CYW43_DEFAULT_PIN_WL_REG_ON 23u
#endif

// gpio pin for spi data out to the cyw43 chip
#ifndef CYW43_DEFAULT_PIN_WL_DATA_OUT
#define CYW43_DEFAULT_PIN_WL_DATA_OUT 24u
#endif

// gpio pin for spi data in from the cyw43 chip
#ifndef CYW43_DEFAULT_PIN_WL_DATA_IN
#define CYW43_DEFAULT_PIN_WL_DATA_IN 24u
#endif

// gpio (irq) pin for the irq line from the cyw43 chip
#ifndef CYW43_DEFAULT_PIN_WL_HOST_WAKE
#define CYW43_DEFAULT_PIN_WL_HOST_WAKE 24u
#endif

// gpio pin for the spi clock line to the cyw43 chip
#ifndef CYW43_DEFAULT_PIN_WL_CLOCK
#define CYW43_DEFAULT_PIN_WL_CLOCK 29u
#endif

// gpio pin for the spi chip select to the cyw43 chip
#ifndef CYW43_DEFAULT_PIN_WL_CS
#define CYW43_DEFAULT_PIN_WL_CS 25u
#endif

pico_board_cmake_set_default(PICO_RP2350_A2_SUPPORTED, 1)
#ifndef PICO_RP2350_A2_SUPPORTED
#define PICO_RP2350_A2_SUPPORTED 1
#endif

#endif
